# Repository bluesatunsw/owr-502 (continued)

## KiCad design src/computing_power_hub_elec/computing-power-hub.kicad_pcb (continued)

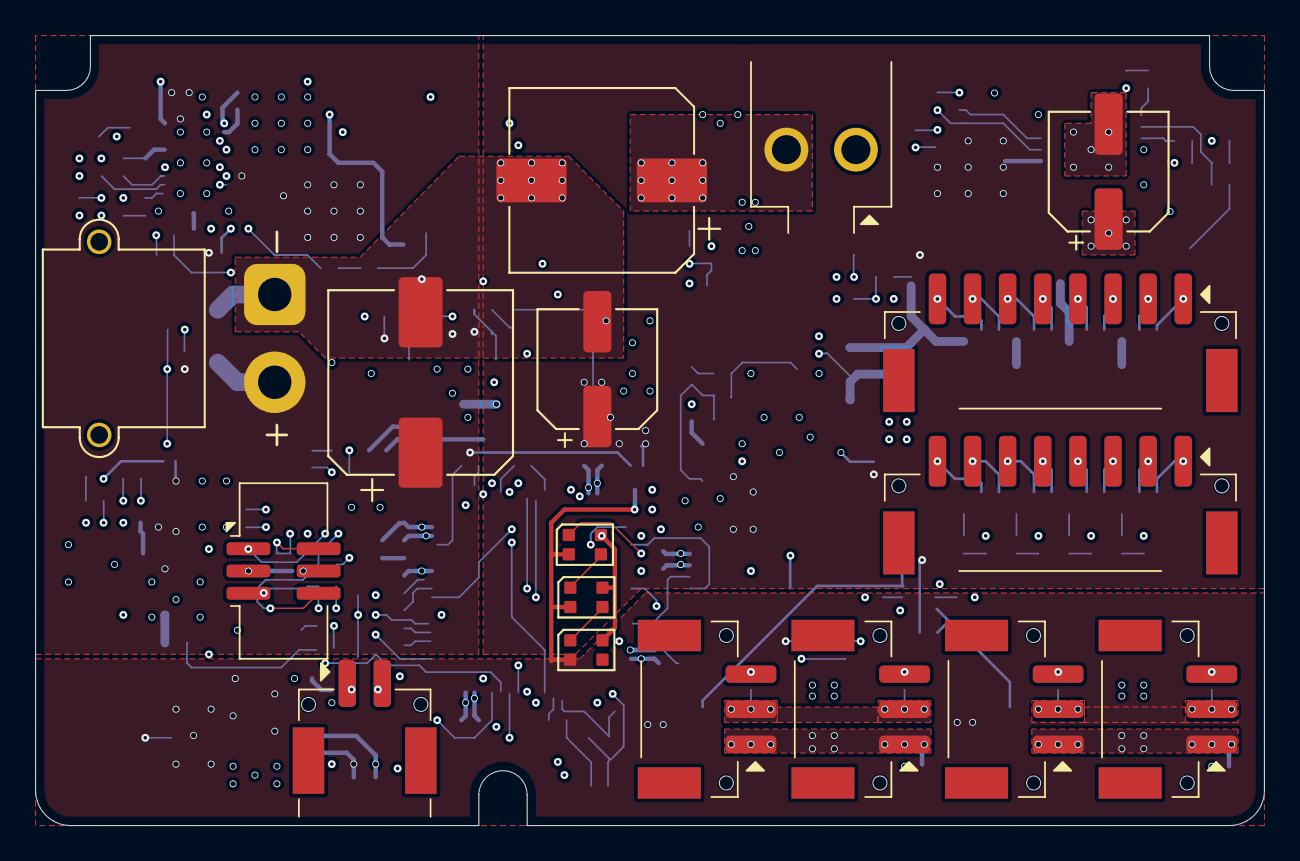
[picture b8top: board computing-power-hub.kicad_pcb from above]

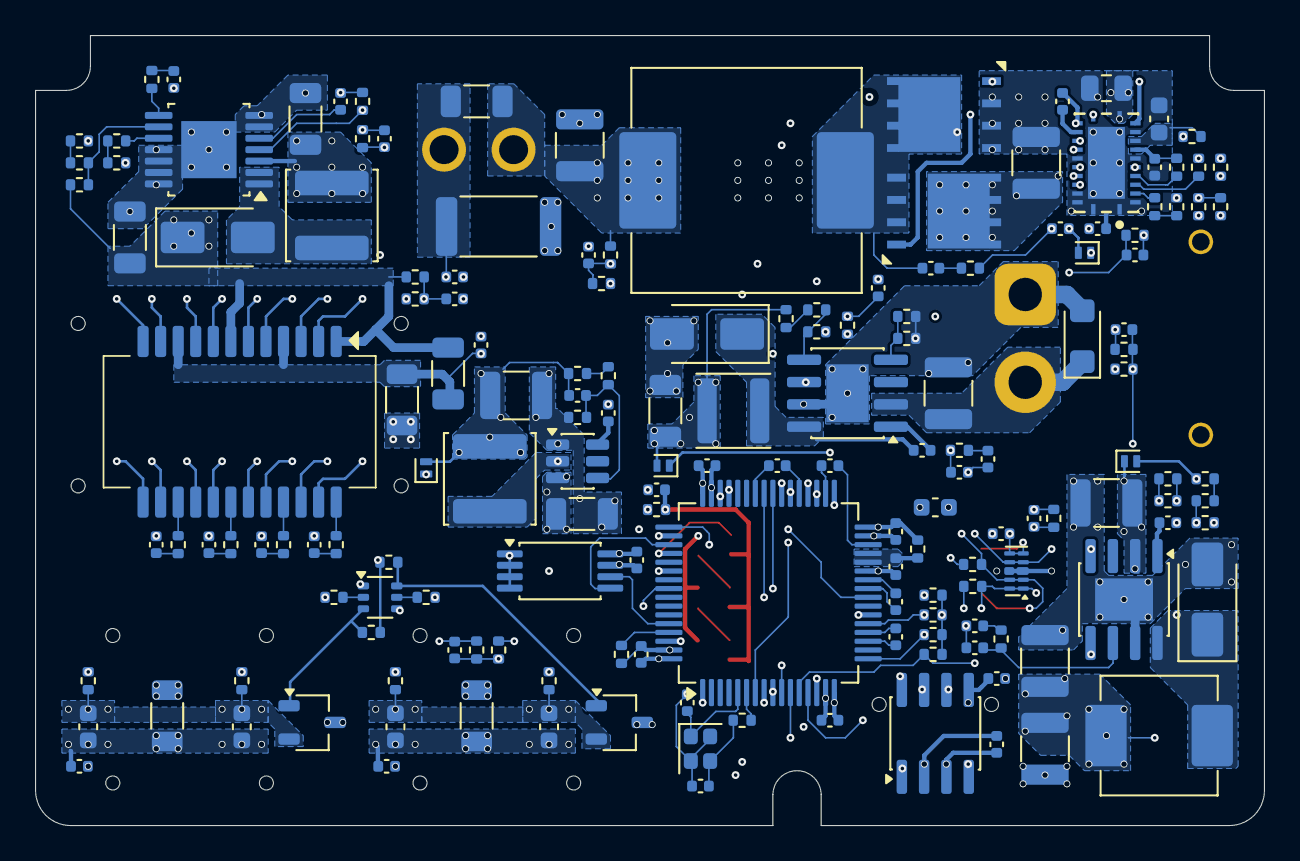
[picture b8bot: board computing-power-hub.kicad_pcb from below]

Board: 6 copper layers, 70.0 x 45.0 mm, 182 parts (165 on the bottom side), 123 nets.

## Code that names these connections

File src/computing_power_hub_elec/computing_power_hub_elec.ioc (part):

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Mcu.Name=STM32G474R(B-C-E)Tx
Mcu.Package=LQFP64
Mcu.UserName=STM32G474RBTx
PA0.GPIOParameters=GPIO_Label
PA0.GPIO_Label=VS_12
PA0.Mode=IN1-Single-Ended
PA0.Signal=ADC1_IN1
PA1.GPIOParameters=GPIO_Label
PA1.GPIO_Label=VS_24
PA1.Mode=IN2-Single-Ended
PA1.Signal=ADC2_IN2
PA11.GPIOParameters=GPIO_Label
PA11.GPIO_Label=CAN_RX
PA11.Mode=FDCAN_Activate
PA11.Signal=FDCAN1_RX
PA12.GPIOParameters=GPIO_Label
PA12.GPIO_Label=CAN_TX
PA12.Mode=FDCAN_Activate
PA12.Signal=FDCAN1_TX
PA13.GPIOParameters=GPIO_Label
PA13.GPIO_Label=SWDIO
PA13.Mode=Trace_Asynchronous_SW
PA13.Signal=SYS_JTMS-SWDIO
PA14.GPIOParameters=GPIO_Label
PA14.GPIO_Label=SWCLK
PA14.Mode=Trace_Asynchronous_SW
PA14.Signal=SYS_JTCK-SWCLK
PA15.GPIOParameters=GPIO_Label
PA15.GPIO_Label=I2C_SCL
PA15.Mode=I2C
PA15.Signal=I2C1_SCL
PA2.GPIOParameters=GPIO_Label
PA2.GPIO_Label=ARGB_I
PA2.Mode=Half_duplex(single_wire_mode)
PA2.Signal=USART2_TX
PA3.GPIOParameters=GPIO_Label
PA3.GPIO_Label=VS_BUS
PA3.Mode=IN4-Single-Ended
PA3.Signal=ADC1_IN4
PA5.GPIOParameters=GPIO_Label
PA5.GPIO_Label=IS_24_M
PA5.Mode=PGA Connected
PA5.Signal=OPAMP2_VINM0
PA6.GPIOParameters=GPIO_Label
PA6.GPIO_Label=IS_24_O
PA6.Signal=SharedAnalog_PA6
PA7.GPIOParameters=GPIO_Label
PA7.GPIO_Label=IS_24_P
PA7.Mode=PGA Connected
PA7.Signal=OPAMP2_VINP
PA8.GPIOParameters=GPIO_Label
PA8.GPIO_Label=IS_5_O
PA8.Signal=SharedAnalog_PA8
PA9.GPIOParameters=GPIO_Label
PA9.GPIO_Label=VS_5
PA9.Mode=IN2-Single-Ended
PA9.Signal=ADC5_IN2
PB0.GPIOParameters=GPIO_Label
PB0.GPIO_Label=IS_19_P
PB0.Mode=PGA Connected
PB0.Signal=OPAMP3_VINP
PB1.GPIOParameters=GPIO_Label
PB1.GPIO_Label=IS_19_O
PB1.Signal=SharedAnalog_PB1
PB10.GPIOParameters=GPIO_Label
PB10.GPIO_Label=IS_12_M
PB10.Mode=PGA Connected
PB10.Signal=OPAMP4_VINM0
PB11.GPIOParameters=GPIO_Label
PB11.GPIO_Label=IS_12_P
PB11.Mode=PGA Connected
PB11.Signal=OPAMP4_VINP
PB12.GPIOParameters=GPIO_Label
PB12.GPIO_Label=IS_12_O
PB12.Signal=SharedAnalog_PB12
PB13.GPIOParameters=GPIO_Label
PB13.GPIO_Label=VS_19
PB13.Mode=IN5-Single-Ended
PB13.Signal=ADC3_IN5
PB14.GPIOParameters=GPIO_Label
PB14.GPIO_Label=TMP_0
PB14.Mode=IN5-Single-Ended
PB14.Signal=ADC1_IN5
PB15.GPIOParameters=GPIO_Label
PB15.GPIO_Label=IS_5_M
PB15.Mode=PGA Connected
PB15.Signal=OPAMP5_VINM0
PB2.GPIOParameters=GPIO_Label
PB2.GPIO_Label=IS_19_M
PB2.Mode=PGA Connected
PB2.Signal=OPAMP3_VINM0
PB3.GPIOParameters=GPIO_Label
PB3.GPIO_Label=SWO
PB3.Mode=Trace_Asynchronous_SW
PB3.Signal=SYS_JTDO-SWO
PB6.GPIOParameters=GPIO_Label
PB6.GPIO_Label=ARGB_2
PB6.Mode=Half_duplex(single_wire_mode)
PB6.Signal=USART1_TX
PB7.GPIOParameters=GPIO_Label
PB7.GPIO_Label=I2C_SDA
PB7.Mode=I2C
PB7.Signal=I2C1_SDA
PB9.GPIOParameters=GPIO_Label
PB9.GPIO_Label=ARGB_3
PB9.Mode=Half_duplex(single_wire_mode)
PB9.Signal=USART3_TX
PC0.GPIOParameters=GPIO_Label
PC0.GPIO_Label=TMP_1
PC0.Mode=IN6-Single-Ended
PC0.Signal=ADC2_IN6
PC1.GPIOParameters=GPIO_Label
PC1.GPIO_Label=TMP_2
PC1.Mode=IN7-Single-Ended
PC1.Signal=ADC1_IN7
PC10.GPIOParameters=GPIO_Label
PC10.GPIO_Label=ARGB_0
PC10.Mode=Half_duplex(single_wire_mode)
PC10.Signal=UART4_TX
PC12.GPIOParameters=GPIO_Label
PC12.GPIO_Label=ARGB_1
PC12.Mode=Half_duplex(single_wire_mode)
PC12.Signal=UART5_TX
PC3.GPIOParameters=GPIO_Label
PC3.GPIO_Label=IS_5_P
PC3.Mode=PGA Connected
PC3.Signal=OPAMP5_VINP
PC4.GPIOParameters=GPIO_Label
PC4.GPIO_Label=TMP_3
PC4.Mode=IN5-Single-Ended
PC4.Signal=ADC2_IN5
PC6.GPIOParameters=GPIO_Label
PC6.GPIO_Label=EN_24
PC6.Signal=GPIO_Output
PC7.GPIOParameters=GPIO_Label
PC7.GPIO_Label=EN_19
PC7.Signal=GPIO_Output
PC8.GPIOParameters=GPIO_Label
PC8.GPIO_Label=EN_12
PC8.Signal=GPIO_Output
PC9.GPIOParameters=GPIO_Label
PC9.GPIO_Label=EN_5
PC9.Signal=GPIO_Output
PF0-OSC_IN.GPIOParameters=GPIO_Label
PF0-OSC_IN.GPIO_Label=HSE_IN
PF0-OSC_IN.Mode=HSE-External-Oscillator
PF0-OSC_IN.Signal=RCC_OSC_IN
PF1-OSC_OUT.GPIOParameters=GPIO_Label
PF1-OSC_OUT.GPIO_Label=HSE_OUT
PF1-OSC_OUT.Mode=HSE-External-Oscillator
PF1-OSC_OUT.Signal=RCC_OSC_OUT
PG10-NRST.GPIOParameters=GPIO_Label
PG10-NRST.GPIO_Label=NRST
PG10-NRST.Signal=GPIO_Input
RCC.HSE_VALUE=8000000
RCC.SYSCLKFreq_VALUE=16000000
board=custom

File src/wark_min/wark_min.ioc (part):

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Mcu.Name=STM32G474R(B-C-E)Tx
Mcu.Package=LQFP64
Mcu.UserName=STM32G474RBTx
PA0.GPIOParameters=GPIO_Label
PA0.GPIO_Label=ENCU
PA0.Signal=S_TIM5_CH1
PA1.GPIOParameters=GPIO_Label
PA1.GPIO_Label=TMPM
PA1.Mode=IN2-Single-Ended
PA1.Signal=ADC1_IN2
PA10.GPIOParameters=GPIO_Label
PA10.GPIO_Label=ENABLE
PA10.Signal=GPIO_Output
PA11.GPIOParameters=GPIO_Label
PA11.GPIO_Label=CAL
PA11.Signal=GPIO_Output
PA12.GPIOParameters=GPIO_Label
PA12.GPIO_Label=FAULT
PA12.Mode=Fault_Enable1
PA12.Signal=HRTIM1_FLT1
PA13.GPIOParameters=GPIO_Label
PA13.GPIO_Label=SWDIO
PA13.Mode=Trace_Asynchronous_SW
PA13.Signal=SYS_JTMS-SWDIO
PA14.GPIOParameters=GPIO_Label
PA14.GPIO_Label=SWCLK
PA14.Mode=Trace_Asynchronous_SW
PA14.Signal=SYS_JTCK-SWCLK
PA15.GPIOParameters=GPIO_Label
PA15.GPIO_Label=I2C_SCL
PA15.Mode=I2C
PA15.Signal=I2C1_SCL
PA2.GPIOParameters=GPIO_Label
PA2.GPIO_Label=ENCW
PA2.Signal=S_TIM5_CH3
PA3.GPIOParameters=GPIO_Label
PA3.GPIO_Label=TMPB
PA3.Mode=IN4-Single-Ended
PA3.Signal=ADC1_IN4
PA4.GPIOParameters=GPIO_Label
PA4.GPIO_Label=VSM
PA4.Mode=IN17-Single-Ended
PA4.Signal=ADC2_IN17
PA5.GPIOParameters=GPIO_Label
PA5.GPIO_Label=VSA
PA5.Mode=IN13-Single-Ended
PA5.Signal=ADC2_IN13
PA6.GPIOParameters=GPIO_Label
PA6.GPIO_Label=QSPI_IO3
PA6.Mode=Dual Bank
PA6.Signal=QUADSPI1_BK1_IO3
PA7.GPIOParameters=GPIO_Label
PA7.GPIO_Label=QSPI_IO2
PA7.Mode=Dual Bank
PA7.Signal=QUADSPI1_BK1_IO2
PA9.GPIOParameters=GPIO_Label
PA9.GPIO_Label=ISA
PA9.Mode=IN2-Single-Ended
PA9.Signal=ADC5_IN2
PB0.GPIOParameters=GPIO_Label
PB0.GPIO_Label=QSPI_IO1
PB0.Mode=Dual Bank
PB0.Signal=QUADSPI1_BK1_IO1
PB1.GPIOParameters=GPIO_Label
PB1.GPIO_Label=QSPI_IO0
PB1.Mode=Dual Bank
PB1.Signal=QUADSPI1_BK1_IO0
PB10.GPIOParameters=GPIO_Label
PB10.GPIO_Label=QSPI_CLK
PB10.Mode=Dual Bank
PB10.Signal=QUADSPI1_CLK
PB11.GPIOParameters=GPIO_Label
PB11.GPIO_Label=QSPI_NCS
PB11.Mode=Enable Chip Select 1 for both banks
PB11.Signal=QUADSPI1_BK1_NCS
PB12.GPIOParameters=GPIO_Label
PB12.GPIO_Label=ISC
PB12.Mode=IN3-Single-Ended
PB12.Signal=ADC4_IN3
PB13.GPIOParameters=GPIO_Label
PB13.GPIO_Label=ISB
PB13.Mode=IN5-Single-Ended
PB13.Signal=ADC3_IN5
PB14.GPIOParameters=GPIO_Label
PB14.GPIO_Label=GLC
PB14.Mode=Output_TD1TD2
PB14.Signal=HRTIM1_CHD1
PB15.GPIOParameters=GPIO_Label
PB15.GPIO_Label=GHC
PB15.Mode=Output_TD1TD2
PB15.Signal=HRTIM1_CHD2
PB2.GPIOParameters=GPIO_Label
PB2.GPIO_Label=VSC
PB2.Mode=IN12-Single-Ended
PB2.Signal=ADC2_IN12
PB3.GPIOParameters=GPIO_Label
PB3.GPIO_Label=SWO
PB3.Mode=Trace_Asynchronous_SW
PB3.Signal=SYS_JTDO-SWO
PB5.GPIOParameters=GPIO_Label
PB5.GPIO_Label=CAN_RX
PB5.Mode=FDCAN_Activate
PB5.Signal=FDCAN2_RX
PB6.GPIOParameters=GPIO_Label
PB6.GPIO_Label=CAN_TX
PB6.Mode=FDCAN_Activate
PB6.Signal=FDCAN2_TX
PB7.GPIOParameters=GPIO_Label
PB7.GPIO_Label=I2C_SDA
PB7.Mode=I2C
PB7.Signal=I2C1_SDA
PB8-BOOT0.GPIOParameters=GPIO_Label
PB8-BOOT0.GPIO_Label=BOOT
PB8-BOOT0.Signal=GPIO_Input
PC0.GPIOParameters=GPIO_Label
PC0.GPIO_Label=TMPA
PC0.Mode=IN6-Single-Ended
PC0.Signal=ADC1_IN6
PC1.GPIOParameters=GPIO_Label
PC1.GPIO_Label=QSPI_IO4
PC1.Mode=Dual Bank
PC1.Signal=QUADSPI1_BK2_IO0
PC10.GPIOParameters=GPIO_Label
PC10.GPIO_Label=ARGB
PC10.Mode=Half_duplex(single_wire_mode)
PC10.Signal=UART4_TX
PC12.GPIOParameters=GPIO_Label
PC12.GPIO_Label=ENCV
PC12.Signal=S_TIM5_CH2
PC2.GPIOParameters=GPIO_Label
PC2.GPIO_Label=QSPI_IO5
PC2.Mode=Dual Bank
PC2.Signal=QUADSPI1_BK2_IO1
PC3.GPIOParameters=GPIO_Label
PC3.GPIO_Label=QSPI_IO6
PC3.Mode=Dual Bank
PC3.Signal=QUADSPI1_BK2_IO2
PC4.GPIOParameters=GPIO_Label
PC4.GPIO_Label=QSPI_IO7
PC4.Mode=Dual Bank
PC4.Signal=QUADSPI1_BK2_IO3
PC5.GPIOParameters=GPIO_Label
PC5.GPIO_Label=VSB
PC5.Mode=IN11-Single-Ended
PC5.Signal=ADC2_IN11
PC6.GPIOParameters=GPIO_Label
PC6.GPIO_Label=GLB
PC6.Mode=Output_TF1TF2
PC6.Signal=HRTIM1_CHF1
PC7.GPIOParameters=GPIO_Label
PC7.GPIO_Label=GHB
PC7.Mode=Output_TF1TF2
PC7.Signal=HRTIM1_CHF2
PC8.GPIOParameters=GPIO_Label
PC8.GPIO_Label=GLA
PC8.Mode=Output_TE1TE2
PC8.Signal=HRTIM1_CHE1
PC9.GPIOParameters=GPIO_Label
PC9.GPIO_Label=GHA
PC9.Mode=Output_TE1TE2
PC9.Signal=HRTIM1_CHE2
PF0-OSC_IN.GPIOParameters=GPIO_Label
PF0-OSC_IN.GPIO_Label=OSC_IN
PF0-OSC_IN.Mode=HSE-External-Oscillator
PF0-OSC_IN.Signal=RCC_OSC_IN
PF1-OSC_OUT.GPIOParameters=GPIO_Label
PF1-OSC_OUT.GPIO_Label=OSC_OUT
PF1-OSC_OUT.Mode=HSE-External-Oscillator
PF1-OSC_OUT.Signal=RCC_OSC_OUT
PG10-NRST.GPIOParameters=GPIO_Label
PG10-NRST.GPIO_Label=NRST
PG10-NRST.Signal=GPIO_Input
RCC.HSE_VALUE=8000000
RCC.SYSCLKFreq_VALUE=16000000
board=custom

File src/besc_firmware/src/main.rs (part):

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    let gpioc = dp.GPIOC.split(&mut rcc);

    // DO NOT MAKE THESE OUTPUTS ON REV. 2P0
    gpiob.pb8.into_input();
    gpiob.pb9.into_analog();

    let mut argb = argb::Controller::new(
        dp.USART1,
        gpioc.pc4.into_alternate(),
        DEFAULT_BRIGHTNESS,
        &mut rcc
    );
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    argb.display(&[RED, RED, RED]);

    let drv = DRV8301::setup(
        gpiob.pb5.into_push_pull_output_in_state(PinState::Low),
        gpiob.pb7.into_floating_input(),
        gpioa.pa15.into_push_pull_output_in_state(PinState::High),
        gpioc.pc10.into_alternate().speed(Speed::VeryHigh),
        gpioc.pc11.into_alternate().speed(Speed::VeryHigh),
        gpioc.pc12.into_alternate().speed(Speed::VeryHigh),
        dp.SPI3,
        &mut rcc,
    );
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    let pwm_driver = STM32G4xxSixPwmDriver::setup(
        &mut rcc,
        dp.TIM1,
        gpioc.pc0.into_alternate(),
        gpioa.pa7.into_alternate(),
        gpioc.pc1.into_alternate(),
        gpiob.pb0.into_alternate(),
        gpioc.pc2.into_alternate(),
        gpiob.pb1.into_alternate(),
        config.motion.idle_mode,
    );

    // Has external 2k2 pullups but ehhhh whatevs
    let hall1 = gpioa.pa2.into_alternate::<2>().internal_pull_up(true);
    let hall2 = gpioa.pa1.into_alternate::<2>().internal_pull_up(true);
    let hall3 = gpioa.pa0.into_alternate::<2>().internal_pull_up(true);

    // Set up hall-sensor interfacing timer (TIM5, 84MHz clock)
    //
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    dp.TIM5.ccer().write(|w| w.cc1e().enabled());

    // Set up ADCs for voltage and motor current sensing.
    // Current sensing: SNA/B/C -> [8301/ext. op amp] -> BR_SO1/2/3 -> PC0/1/2
    // NOTE: SNC/BR_SO3/PC2 not currently used because the 3rd phase current sense op amp doesn't work.
    // Use injected channels (see README) in dual ADC mode (=> simultaneous conversion), using a
    // different ADC peripheral (ADC1/2/3) for each phase.
    // TIM1 OC4 or TIM1 TRGO?
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    }
    let driver = CanDriver::new(
        dp.FDCAN1,
        gpioa.pa11.into_alternate(),
        gpioa.pa12.into_alternate(),
        &mut rcc
    );
    let transmitter = CanTransmitter::new(canadensis_can::Mtu::CanFd64);
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
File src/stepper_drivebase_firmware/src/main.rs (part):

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    let gpioc = dp.GPIOC.split(&mut rcc);
    let gpiod = dp.GPIOD.split(&mut rcc);

    // Set PB8 to output mode to limit power consumption on reset
    gpiob.pb8.into_push_pull_output();

    // Initialise various device drivers.
    let mut argb = argb::Controller::new(
        dp.USART1,
        gpiob.pb6.into_alternate(),
        DEFAULT_BRIGHTNESS,
        &mut rcc,
    );
    let clock = clock::MicrosecondClock::new(dp.TIM2, &mut rcc);
    let can = CanDriver::new(
        dp.FDCAN1,
        gpioa.pa11.into_alternate(),
        gpioa.pa12.into_alternate(),
        &mut rcc,
    );

    let mut drivebase = Drivebase::new(
        (
            gpioc.pc10.into_alternate(),
            gpioc.pc11.into_alternate(),
            gpioc.pc12.into_alternate(),
        ),
        StepperNcsPins(
            gpiob
                .pb9
                .into_push_pull_output_in_state(PinState::High)
                .into(),
            gpioc
                .pc13
                .into_push_pull_output_in_state(PinState::High)
                .into(),
            gpioc
                .pc14
                .into_push_pull_output_in_state(PinState::High)
                .into(),
            gpioc
                .pc15
                .into_push_pull_output_in_state(PinState::High)
                .into(),
        ),
        gpioa.pa8.into_analog(),
        gpiod.pd2.into_push_pull_output(),
        gpioa.pa10.into_input(),
        // Currently, the encoder does not work.
        // TODO: fix encoder, uncomment this when working
        (
            gpiob.pb13.into_alternate(),
            gpiob.pb14.into_alternate(),
            gpiob.pb15.into_alternate(),
        ),
        encoder_bus::EncoderNcsPins(
            gpioc
                .pc6
                .into_push_pull_output_in_state(PinState::High)
                .into(),
            gpioc
                .pc7
                .into_push_pull_output_in_state(PinState::High)
                .into(),
            gpioc
                .pc8
                .into_push_pull_output_in_state(PinState::High)
                .into(),
            gpioc
                .pc9
                .into_push_pull_output_in_state(PinState::High)
                .into(),
        ),
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
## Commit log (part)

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2025-11-29 Revert "schematic work"
    This reverts commit 45c2a37584fa5a23125d2ab6619b00460526ce77.
2025-11-29 progress
2025-11-29 Stole some schematics, will copy paste into master schematic later
2025-11-29 more work
2025-12-02 [VESC] Swap phase A and C MOSFET labels (#123)
2025-12-02 Fix rotated IDC6 on CPM/MPM/VESC/Stepper/USB Hub
2025-12-02 Fix rotated IDC6 on CPM/MPM/VESC/Stepper/USB Hub (#120)
    * Fix rotated IDC6 on CPM/MPM/VESC/Stepper/USB Hub
    * Fix VESC
2025-12-10 Add scaled versions of other footprints (vibes mech)
2025-12-20 finished power board
2026-01-16 Fix STB on can trans for CPH
2026-01-16 Fix StepDriv Can trans
2026-01-16 Fix can trans (#126)
    * Fix STB on can trans for CPH
    * Fix MPM can trans
    * Fix StepDriv Can trans
    * Fix can trans on UPB
2026-01-28 Pull in embedded common utils from the bootloader branch
2026-01-29 Fix formatting of comments explaining UART/WS2812 lookup table
2026-01-29 Add utils common to all devices to a shared library (#128)
    * Pull in embedded common utils from the bootloader branch
    * Remove SplitController and Led, move buffer outside of Controller
    * Fix formatting of comments explaining UART/WS2812 lookup table
    ---------
2026-01-29 Fix AMBER colour in embedded_common (#129)
2026-02-02 Initial commit w basic canadensis loop; RGB LEDs WIP
2026-02-02 [HW untested] Stepper driver WIP, ADC temperature readings, SPI prelim
2026-02-02 Add IMU functions and errors
2026-02-02 Add .gitignore
2026-02-02 Improve RGB LED hardware drriver implementation
2026-02-02 Initial bringup code, thankq Jonah
2026-02-02 Aavin my sweet princess save me (ADC)
2026-02-02 Get RGB LED driver working and re-organise code
2026-02-02 Updated Cargo.toml with jonah's fixed crate, fixed impl
2026-02-02 Remove unused packages
2026-02-02 Changed tests, leds not working
2026-02-02 Minor changes for my laptop
2026-02-02 Updated ioc file
2026-02-02 More SPI work, untested
2026-02-02 Fix name of ISM330
2026-02-02 Refactor to use embedded_common
2026-02-06 Test encoder, finish adjust() function
2026-02-06 Refactor stepper public interface
2026-02-06 BUllshit
2026-02-06 YOLO encoder stuff, general style cleanup
2026-02-06 Read ID sequence from QSPI
2026-02-06 YOLO I2C functionality
2026-02-06 Implement memory mapping for QSPI flash with basic test code
2026-02-06 Add MCO output
2026-02-06 Receives can command and runs, however has a stalling problem
2026-02-06 Nicer interface for interacting with TMCs
2026-02-06 Stepper driver works!
2026-02-06 Make all the steppers go
2026-02-06 Stuff until I got bored
2026-02-06 [TESTED] Drop Vmax to 50RPS, fix node name, remove hprintlns
2026-02-07 Comment out encoder stuff with reasoning
2026-02-07 Stepper drivebase firmware (#124)
    Credits:
    Firmware Pioneer - Jonah
    Cyphal Whisperer - Jonah
    I2C 2IC - Kai
    QSPI Wizard - Evan
    Professional Refactoring, Inc. - Jethro, Evan, Aavin
2026-02-07 more progress
2026-02-08 Checkpoint
2026-02-08 Hiiiiiiiiiiiiiiiii
2026-02-08 Features which came to me in a dream
2026-02-08 Literacy my greatest enemy
2026-02-08 Small pile becomes big pile
2026-02-08 Pre-stupid
2026-02-08 Format bootloader and get working with real elec_common
2026-02-09 Add initialization scripts for OBC (#132)
2026-02-09 update scripts
2026-02-09 Fix init.bash to be runnable from anywhere
2026-02-09 Fix simulation, format files
2026-02-09 Fix control_station readme
2026-02-09 Scuffed angle optimization code, limit to ±90 deg
2026-02-09 Moar progress
2026-02-09 Make mock cyphal VESC driver to test integration, pipe it up in rover pkg
2026-02-09 Invert steppers to be CCW +ve
2026-02-10 [progress]
2026-02-10 Remove fun :(
2026-02-12 Status codes based on TMC errors
2026-02-14 Reinvent the wheel
2026-02-14 Glorp operator respect button ----> (Fix the SM0*B-PASS connectors type shit)
2026-02-14 Glorp operator respect button ----> (Fix the SM0*B-PASS connectors type shit) (#142)
2026-02-18 Add note about running in prod
2026-02-18 Add VESC firmware in correct format: sowwy Jonah
2026-02-18 Update debug/run instructions
2026-02-18 Explain what bsp/ state/ and config/ are
2026-02-18 Slight refactor to add preset configurations
2026-02-21 Add a script to export stencils
2026-02-21 elec_common library cleanup (#146)
    Footprints:
    - Added extra common pads (9, 10) to the 6-in-1 USB TVS diodes (footprint UDFN8_3P3X1_517CB_QNS)
    - Can someone check the solder paste layer is sensible?
    - Created improved PowerPAD footprint for the TPS61175
    Symbols:
    - Deleted unused and unstocked TPS565201 symbol
2026-02-23 Update WS2812-2020 footprint, add WS2812B-5050 footprint
2026-02-23 Update WS2812-2020 footprint, add WS2812B-5050 footprint (#156)
2026-02-27 Properly license code for open sourcing
2026-02-27 Additional KiCAD files
2026-02-28 Add extra debug utils
2026-02-28 Add extra debug utils (#163)
2026-02-28 Fix bypass caps lmao
2026-02-28 Comply with versioning scheme
2026-02-28 LED Beacon finished
2026-02-28 Add changelog and small changes
2026-02-28 Clean up (fix footprints, DRC etc.) for production
2026-02-28 Change 0.3/0.4 mm vias to 0.3/0.45 for JLC
2026-02-28 Fucking
2026-02-28 routing + change buck IC
2026-02-28 Add safiy's files
2026-02-28 Comply with versioning scheme, add silkscreen art
2026-02-28 Small changes
2026-02-28 Changes to footprint library
2026-02-28 Layout
2026-02-28 Clean up for production (purely cosmetic fixes save for shifting some vias slightly to the left for clearance)
2026-02-28 Before...
2026-02-28 Sean has been collared
2026-02-28 MIXED UP RADIUS AND DIAMETER OOPSIE
2026-02-28 Not any less stupid, add some silkscreen art
2026-02-28 Perfect DRC and silkscreen removed from bottom
2026-02-28 Remove log files
2026-02-28 Fixed MPM schematic as per errata from 4th Feb 2026
2026-02-28 Almost done routing
2026-02-28 Finished routing
2026-02-28 Perfect footprint pass and DRC pass, successful rebase and fix, ready to order, SEAN
2026-02-28 Small routing changes
2026-02-28 Removed unnecessary ioc file
2026-02-28 Fix top silkscreen and add silkscreen art
2026-02-28 Fix SPM schematic as per errata 04-02-2026
2026-02-28 Prepattern
2026-02-28 Added libs for SPM
2026-02-28 Draft SPM PCB layout
2026-02-28 Added system power hub kicad project stuff
2026-02-28 Cleaned up routing and adjusted PCB layout
    - Moved components at least 1.5mm away from board edge
    - Adjusted board size slightly for more clearance
    - Removed pullups for eeprom
    - Adjusted via sizing, made some smaller
2026-02-28 Updated SPM channels to reflect MPM changes
    - Added schottky to vdrive path
    - Modified schottky diodes to be sod 882 (SBR0240LP-7)
    - Changed 100n capacitor connection to NMOS source
    - Updated routing accordingly
    - Minor DRC fixes
2026-02-28 Remove unused files / logs
2026-02-28 Fix vias 0.3/0.4 to 0.3/0.45
2026-02-28 configure STM32G4 and route
2026-02-28 Finish schem bar mosfet footprints
2026-02-28 Fix small global label error
2026-02-28 Setup Vesc2 files
2026-02-28 Configured STM32 IOC file for outputs
2026-02-28 recreate gate driver looking less ugly
2026-02-28 Change mounting holes and remove can diode
2026-02-28 Add mounting holes to corners of board
2026-02-28 BESC Silkscreen art and version number
2026-02-28 Update footprints of connectors and reroute
2026-02-28 [ELEC] CPM v2.0 (#148)
    * Add changelog and small changes
    * aaa
    * I remember
    * Fucking
    * Silky
    * Delete src/computing_power_hub_elec/CHANGELOG.md
2026-02-28 [ELEC] Stepper board v3.0 (#147)
    * Significantly reduce the number of components based on testing data
    * Before...
    * fff
    * Layout
    * Silkscreen
    * にゃー
2026-02-28 [ELEC] Neo adaptor v1.0 (#149)
    * Stupid fvcking NEO adaptor
    * Not any less stupid, add some silkscreen art
    * MIXED UP RADIUS AND DIAMETER OOPSIE
    * Sean has been collared
2026-02-28 [ELEC] System power board v1.0 (#152)
    * Added system power hub kicad project stuff
    * Added libs for SPM
    * [WIP] Copied KiCAD proj from MPM, modified schematic for SPM
    * Removed unnecessary ioc file
    * Draft SPM PCB layout
    * Fixed XT connector routing, rewired power stuff (attempted to), made board smaller, more routing/layout progress
2026-02-28 [ELEC] Led beacon (#154)
    * Setup led_beacon file for someone to work on it eyes emoji
    * Add readme and board dimentions in the PCB
    * LED Beacon finished
    * Move LED beacon to correct folder
    * Fix bypass caps lmao
    * Comply with versioning scheme
2026-02-28 dprintln flag
2026-02-28 Add basic CI pipeline for elec
2026-02-28 Switch to cached image
2026-02-28 Nicer printing
2026-02-28 Try skip 3d libraries
2026-02-28 Check exit properly
2026-02-28 Add basic CI pipeline for elec (#165)
    * Add basic CI pipeline for elec
    * Fix trigger
    * Switch to cached image
    * Fix path
    * Fix path
    * Nicer printing
2026-03-01 Update deps
2026-03-01 Split up control mode, readd logging gated by dprintln-enabled
2026-03-01 Add & impl brake/coast mode config thru TIMx.CHx.OSSI
2026-03-02 Add functions for logging values (eg. u32s), bytes and hexdumps over the (#167)
    eye tee em
2026-03-02 Pull in bootloader from the fucked branch
2026-03-02 Oops
2026-03-03 I'm Aavin's good boy :smile: (#169)
2026-03-04 Brake/Coast mode works
2026-03-06 Additional Progress on motherboard
2026-03-07 Factor out TMC interfacing code into a common library (#170)
2026-03-07 Add documentation comments to all TMC registers (#171)
2026-03-07 Create arm stepper
2026-03-11 Add support for arithmetic operations TMC unit types
2026-03-11 Format file
2026-03-12 Implement basic linac control
2026-03-12 Velocity and position rollover detection (mostly working)
2026-03-12 Actually use glitch accumulator
2026-03-18 Bump firmware and hardware version
2026-03-20 caninit.sh set txqueuelen=1000
2026-03-20 [OBC] arm script
2026-03-20 Change LED indexes for r2p0
2026-03-21 Clear interrupt on hall effect glitch decision
2026-03-24 Invert drivebase r3p0 stepper_drivebase_firmware
2026-03-24 Tested on rover, flip some knobs
2026-03-24 Actually commit current limits (I think)
2026-03-24 Re-add unique colour pattern
2026-03-25 Add encoders back into the mix
2026-03-25 BESC CAN downgrade from FD to classic for comp drivebase compatibility
2026-03-26 Report the current stepper angle from the TMCs
2026-03-27 Report the current stepper angle from the TMCs (#175)
    * Report the current stepper angle from the TMCs
    * Start publishing the position messages
2026-03-27 Ignore mediamtx
2026-03-27 Obc utils (#176)
    * caninit.sh set txqueuelen=1000
    * Minorly update wasd and run_steering script, remove tankcontrol.sh, change wasd speeds, add kinect to Udev rules
    * [OBC] arm script
    * Update OBC utils for comp
    * Ignore mediamtx
    ---------
2026-03-27 Anti-spam (#177)
2026-03-27 Disable telem
2026-03-27 Disable telem (#178)
2026-03-27 Consolidate motor commands into sets of 4
2026-03-27 Initial commit of deckard
2026-03-27 Patch in CANFD support on Linux
2026-03-27 More unmaintainable bs
2026-03-27 Attempt to fix wheel drive directions
2026-03-27 Remove binary blob
2026-03-27 Remove random changes
2026-03-27 Skip steering wheels if they're already in position
2026-03-27 Fixed /dev/video remapping to persistent names
2026-03-27 Fixed /dev/video remapping to persistent names (#181)
2026-03-27 Get new camera scheme working on rover, sorry for merging early aavin (#182)
2026-04-07 Firmware`1
2026-04-11 Add hardware errata template
